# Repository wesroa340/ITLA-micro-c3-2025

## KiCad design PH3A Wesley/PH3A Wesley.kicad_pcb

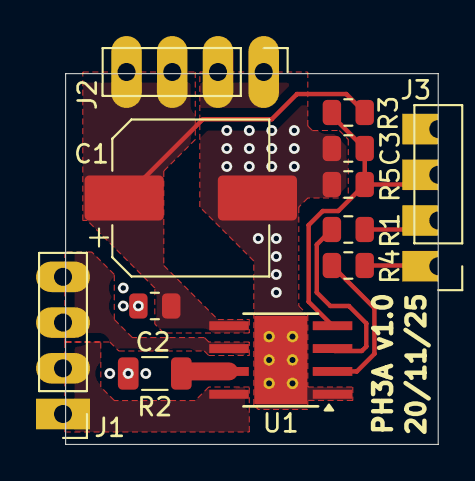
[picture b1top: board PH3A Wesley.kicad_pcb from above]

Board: 2 copper layers, 20.7 x 20.6 mm, 12 parts (0 on the bottom side), 10 nets.

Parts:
C1: C_Polarized; CP_Elec_8x10.5
C2, C3: C; R_0805_2012Metric
J1, J2, J3: Conn_01x04_Pin; PinHeader_1x04_P2.54mm_Vertical
R1, R3, R4, R5: R; R_0805_2012Metric
R2: R; C_1206_3216Metric
U1: DRV8870DDA; Texas_HTSOP-8-1EP_3.9x4.9mm_P1.27mm_EP2.95x4.9mm_Mask2.4x3.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

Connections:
/IN1: J3.2, R1.1
/IN2: J3.1, R4.1
/ISEN: R2.1, U1.7 (ISEN)
/OUT1: J1.3, J1.4, U1.6 (OUT1)
/OUT2: J1.1, J1.2, U1.8 (OUT2)
/VREF: C3.1, J3.3, R3.2, R5.1, U1.4 (VREF)
GND: C1.2, C2.2, C3.2, J2.1, J2.2, J3.4, R2.2, R5.2, U1.1 (GND), U1.9 (GND)
unnamed: R1.2, U1.3 (IN1)
unnamed: R4.2, U1.2 (IN2)
VCC: C1.1, C2.1, J2.3, J2.4, R3.1, U1.5 (VM)

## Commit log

2025-10-10 yupi
2025-10-11 :) lo logre
2025-10-11 ta dificil
2025-10-18 cine
2025-11-12 vamos alla
2025-11-24 YEAH
2025-11-24 siiiii
